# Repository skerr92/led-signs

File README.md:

# Create Custom LED Signs!

Welcome to my custom LED signs project! This project is designed to help people get into electronics and introduced with simple circuit design.

Included in this repository is a wealth of resources to get started. There are some basic circuit diagrams, Eagle board designs for simple signs, and starter code with sign animations.

Over time, more designs and resources will be added to the project to be used as you pleased for <b>Personal Use Only</b>. We would love for other users to add on to this project and create new ways for new users to explore circuit design and electronics.

# How to get started

<ol>
  <li>Checkout the Circuit Diagrams</li>
  <li>Download the Eagle Files</li>
  <li>customize as you see fit</li>
</ol>

# Checkout the Circuit Diagrams

Before getting started, it is important to get an understanding of the basic circuit that is used to drive the basic designs presented in this repository.
This understanding will help you determine what is necessary to make these circuits work. I would suggest getting familiar with Ohm's Law, principles of diodes, characteristics of capacitors, and current gain relationship of transistors. These concepts are fundamental for the operation of these LED arrays.

You can go to websites like <a href="https://circuitlab.com">circuitlab</a> to build circuits and get acquainted with modeling circuits and simulating them as well.

# Download the Eagle Files

Downloading the eagle files will allow you to open the project in Autodesk Eagle which comes with Fusion360.

You can get a hobbyist 1 year trial of <a href="https://www.autodesk.com/campaigns/fusion-360-for-hobbyists">Eagle Here!</a>

In eagle you can open the schematics and board designs to see the layout.

# Customize as you see fit

After you get used to working with the circuits provided with this project, customize them to what you need! Design additional letters, or make cool shapes! The only limitation is your imagination! (and your board size, but you can always get a bunch of boards to put together!)

# Questions?

Email: <a href="mailto:thesethkerr@gmail.com">thesethkerr@gmail.com</a>

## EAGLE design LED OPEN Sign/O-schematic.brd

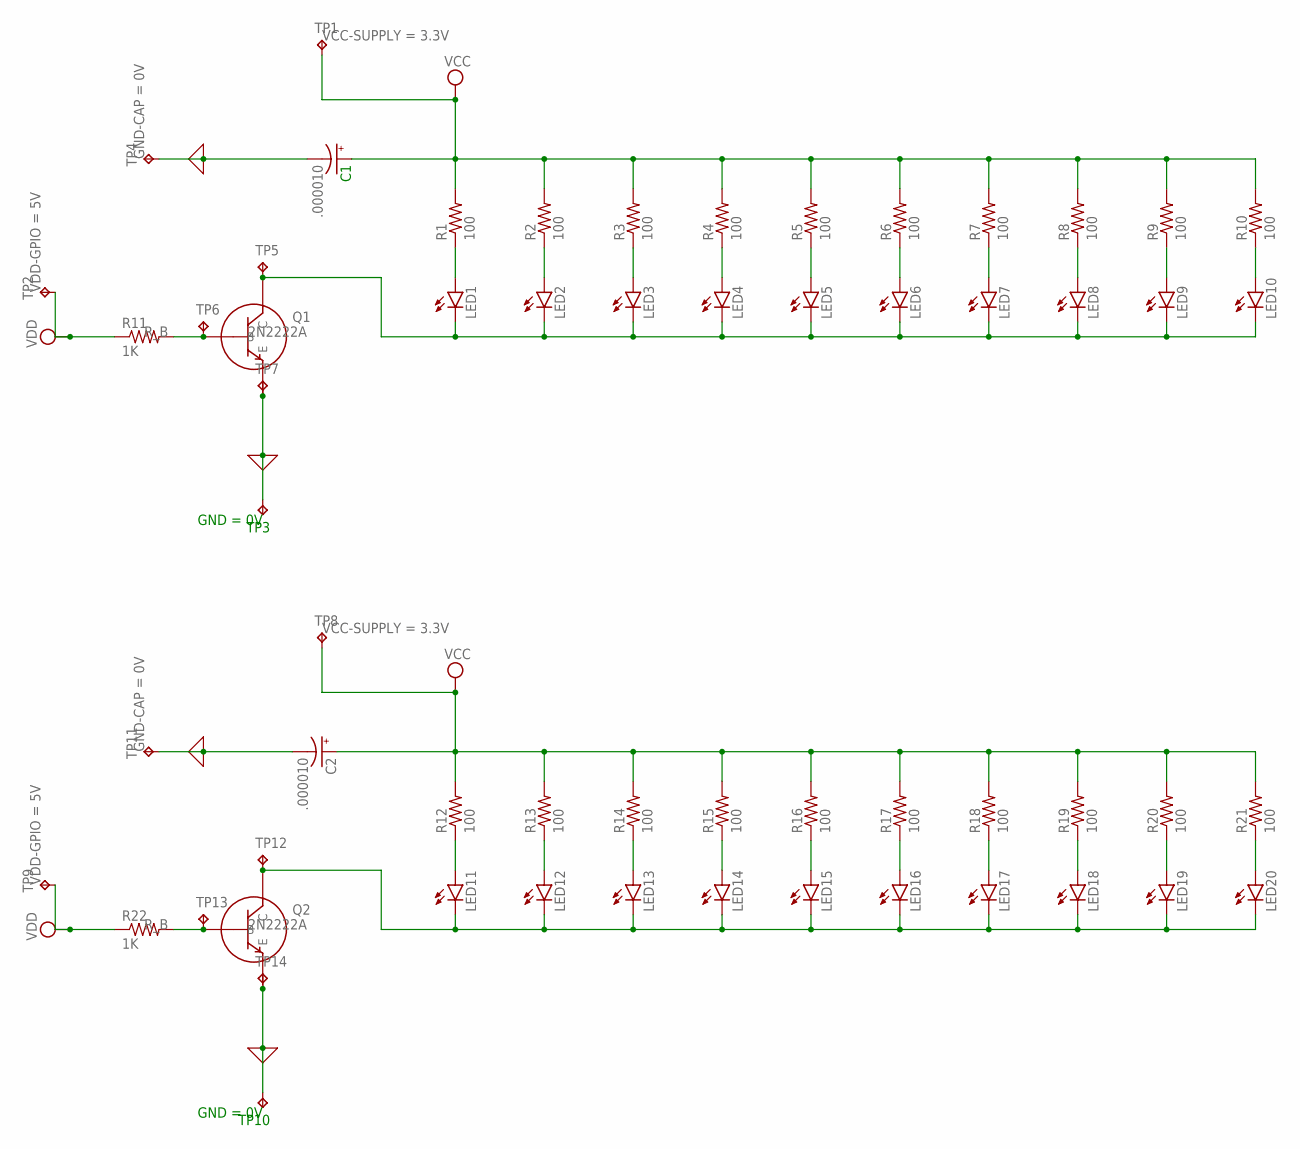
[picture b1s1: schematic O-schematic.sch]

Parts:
C1: .000010; E2,5-6
C2: .000010; E2,5-5
LED1, LED2, LED3, LED4, LED5, LED6, LED7, LED8, LED9, LED10, LED11, LED12, LED13, LED14, LED15, LED16, LED17, LED18, LED19, LED20: LEDCHIPLED-0603-TTW; CHIPLED-0603-TTW
R1, R2, R3, R4, R5, R6, R7, R8, R9, R10, R12, R13, R14, R15, R16, R17, R18, R19, R20, R21: 100; R0603
R11, R22: 1K; R0603
TP1, TP2, TP3, TP4, TP8, TP9, TP10, TP11: TPPAD1-13Y; P1-13Y
TP5, TP6, TP7, TP12, TP13, TP14: TPPAD1-13; P1-13

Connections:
0: C1.-, C2.-, TP3.TP, TP4.TP, TP7.TP, TP10.TP, TP11.TP, TP14.TP
unnamed: R11.2, TP6.TP
unnamed: LED1.C@1 (C), LED2.C@1 (C), LED3.C@1 (C), LED4.C@1 (C), LED5.C@1 (C), LED6.C@1 (C), LED7.C@1 (C), LED8.C@1 (C), LED9.C@1 (C), LED10.C@1 (C), TP5.TP
unnamed: LED1.A@1 (A), R1.1
unnamed: LED2.A@1 (A), R2.1
unnamed: LED3.A@1 (A), R3.1
unnamed: LED4.A@1 (A), R4.1
unnamed: LED5.A@1 (A), R5.1
unnamed: LED6.A@1 (A), R6.1
unnamed: LED7.A@1 (A), R7.1
unnamed: LED10.A@1 (A), R10.1
unnamed: LED9.A@1 (A), R9.1
unnamed: LED8.A@1 (A), R8.1
unnamed: R22.2, TP13.TP
unnamed: LED11.C@1 (C), LED12.C@1 (C), LED13.C@1 (C), LED14.C@1 (C), LED15.C@1 (C), LED16.C@1 (C), LED17.C@1 (C), LED18.C@1 (C), LED19.C@1 (C), LED20.C@1 (C), TP12.TP
unnamed: LED11.A@1 (A), R12.1
unnamed: LED12.A@1 (A), R13.1
unnamed: LED13.A@1 (A), R14.1
unnamed: LED14.A@1 (A), R15.1
unnamed: LED15.A@1 (A), R16.1
unnamed: LED16.A@1 (A), R17.1
unnamed: LED17.A@1 (A), R18.1
unnamed: LED20.A@1 (A), R21.1
unnamed: LED19.A@1 (A), R20.1
unnamed: LED18.A@1 (A), R19.1
VCC: C1.+, C2.+, R1.2, R2.2, R3.2, R4.2, R5.2, R6.2, R7.2, R8.2, R9.2, R10.2, R12.2, R13.2, R14.2, R15.2, R16.2, R17.2, R18.2, R19.2, R20.2, R21.2, TP1.TP, TP8.TP
VDD: R11.1, R22.1, TP2.TP, TP9.TP

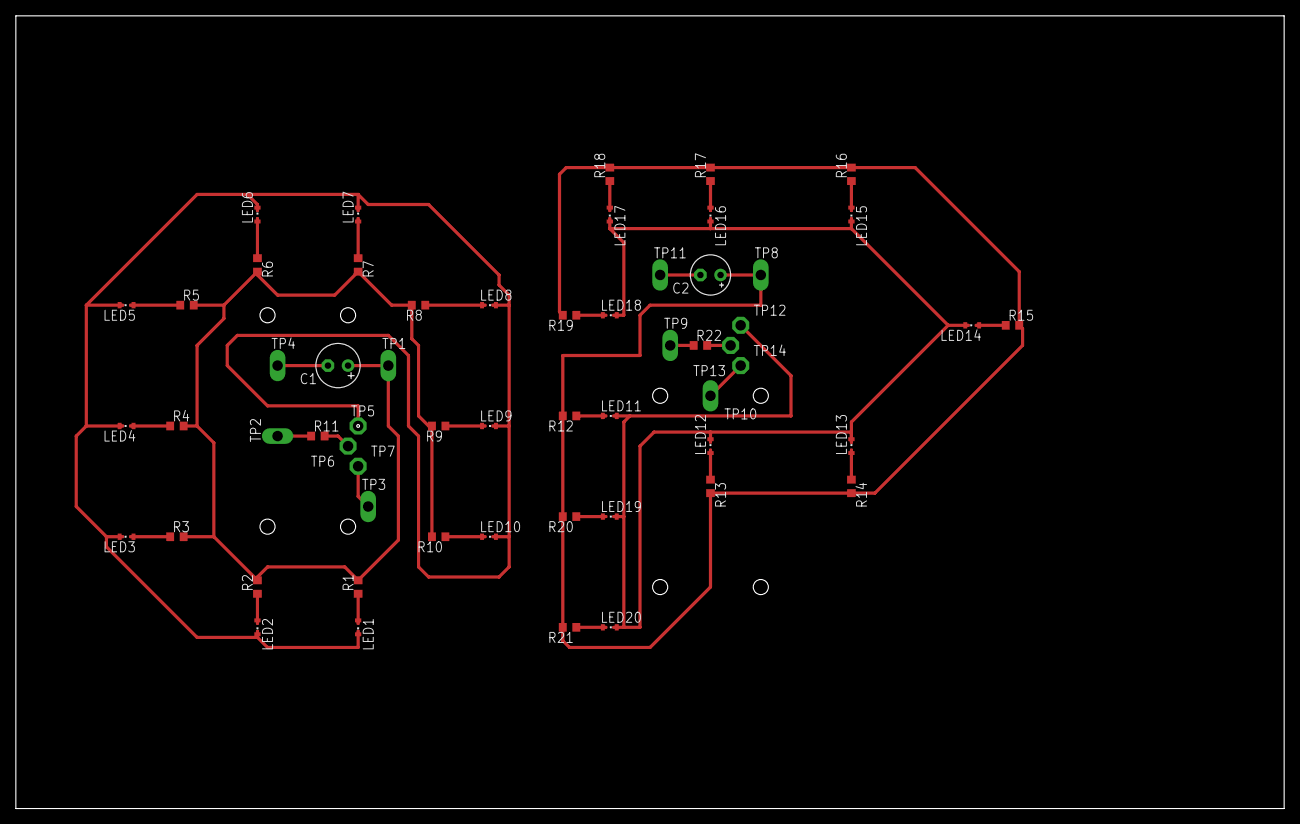
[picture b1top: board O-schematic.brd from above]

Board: 2 copper layers, 160.0 x 100.0 mm, 58 parts (0 on the bottom side), 27 nets.

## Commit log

2020-02-21 Update README.md
    Updating main readme file.
